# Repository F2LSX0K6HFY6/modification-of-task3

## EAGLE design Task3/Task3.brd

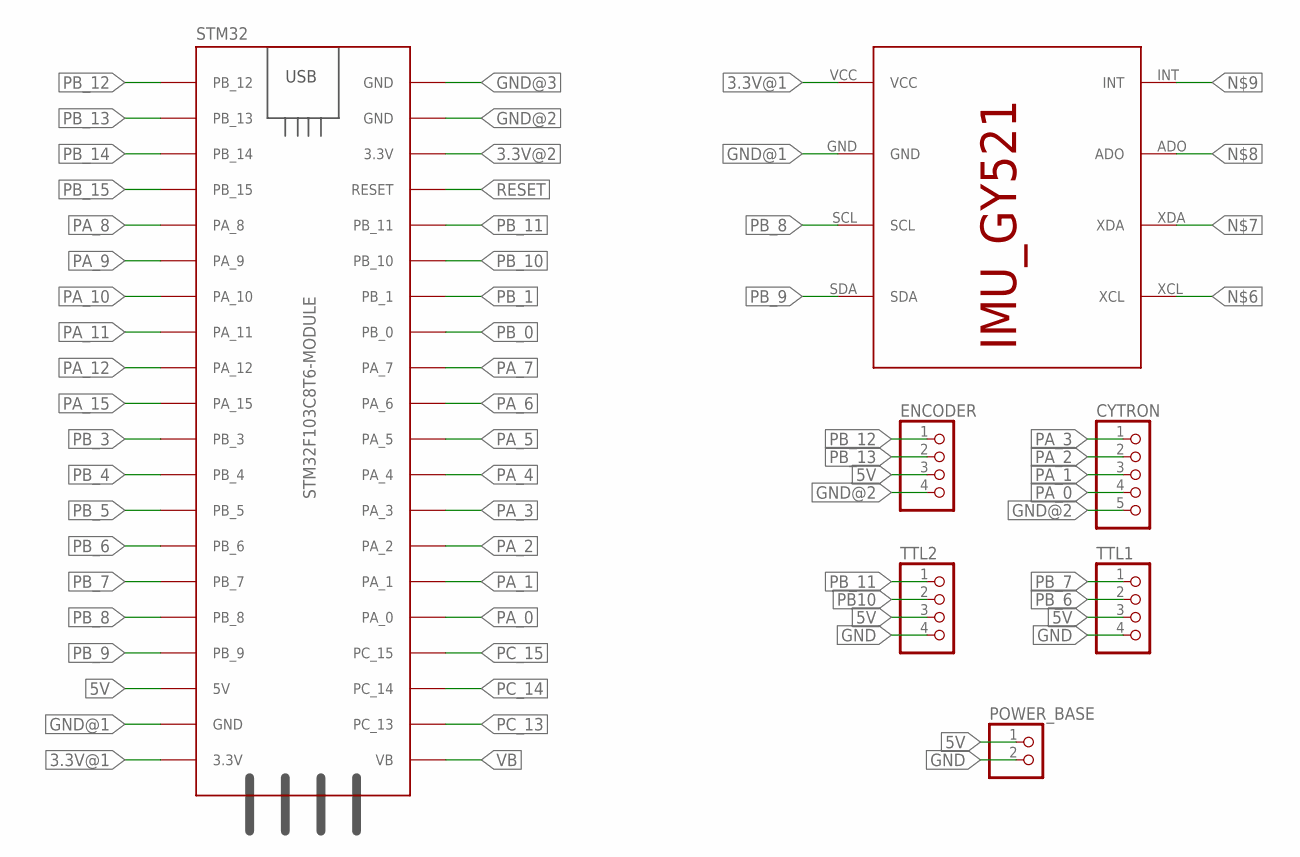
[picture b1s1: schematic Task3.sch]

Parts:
CYTRON: PINHD-5_DATA; 1X05_DATA
ENCODER: PINHD-4_DATA; 1X04_DATA
POWER_BASE: PINHD-2_DATA; 1X02_DATA
STM32: STM32F103C8T6-MODULE
TTL1, TTL2: PINHD-4_DATA; 1X04_DATA
U$1: IMU_ROBOCON_GY521; IMU_GY521

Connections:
3.3V@1: STM32.3.3V_1 (3.3V), U$1.VCC
3.3V@2: STM32.3.3V_2 (3.3V)
5V: ENCODER.3, POWER_BASE.1, STM32.5V, TTL1.3, TTL2.3
GND: POWER_BASE.2, TTL1.4, TTL2.4
GND@1: STM32.GND_1 (GND), U$1.GND
GND@2: CYTRON.5, ENCODER.4, STM32.GND_2 (GND)
GND@3: STM32.GND_3 (GND)
PA_0: CYTRON.4, STM32.PA_0
PA_1: CYTRON.3, STM32.PA_1
PA_2: CYTRON.2, STM32.PA_2
PA_3: CYTRON.1, STM32.PA_3
PA_4: STM32.PA_4
PA_5: STM32.PA_5
PA_6: STM32.PA_6
PA_7: STM32.PA_7
PA_8: STM32.PA_8
PA_9: STM32.PA_9
PA_10: STM32.PA_10
PA_11: STM32.PA_11
PA_12: STM32.PA_12
PA_15: STM32.PA_15
PB10: TTL2.2
PB_0: STM32.PB_0
PB_1: STM32.PB_1
PB_3: STM32.PB_3
PB_4: STM32.PB_4
PB_5: STM32.PB_5
PB_6: STM32.PB_6, TTL1.2
PB_7: STM32.PB_7, TTL1.1
PB_8: STM32.PB_8, U$1.SCL
PB_9: STM32.PB_9, U$1.SDA
PB_10: STM32.PB_10
PB_11: STM32.PB_11, TTL2.1
PB_12: ENCODER.1, STM32.PB_12
PB_13: ENCODER.2, STM32.PB_13
PB_14: STM32.PB_14
PB_15: STM32.PB_15
PC_13: STM32.PC_13
PC_14: STM32.PC_14
PC_15: STM32.PC_15
RESET: STM32.RESET
VB: STM32.VB

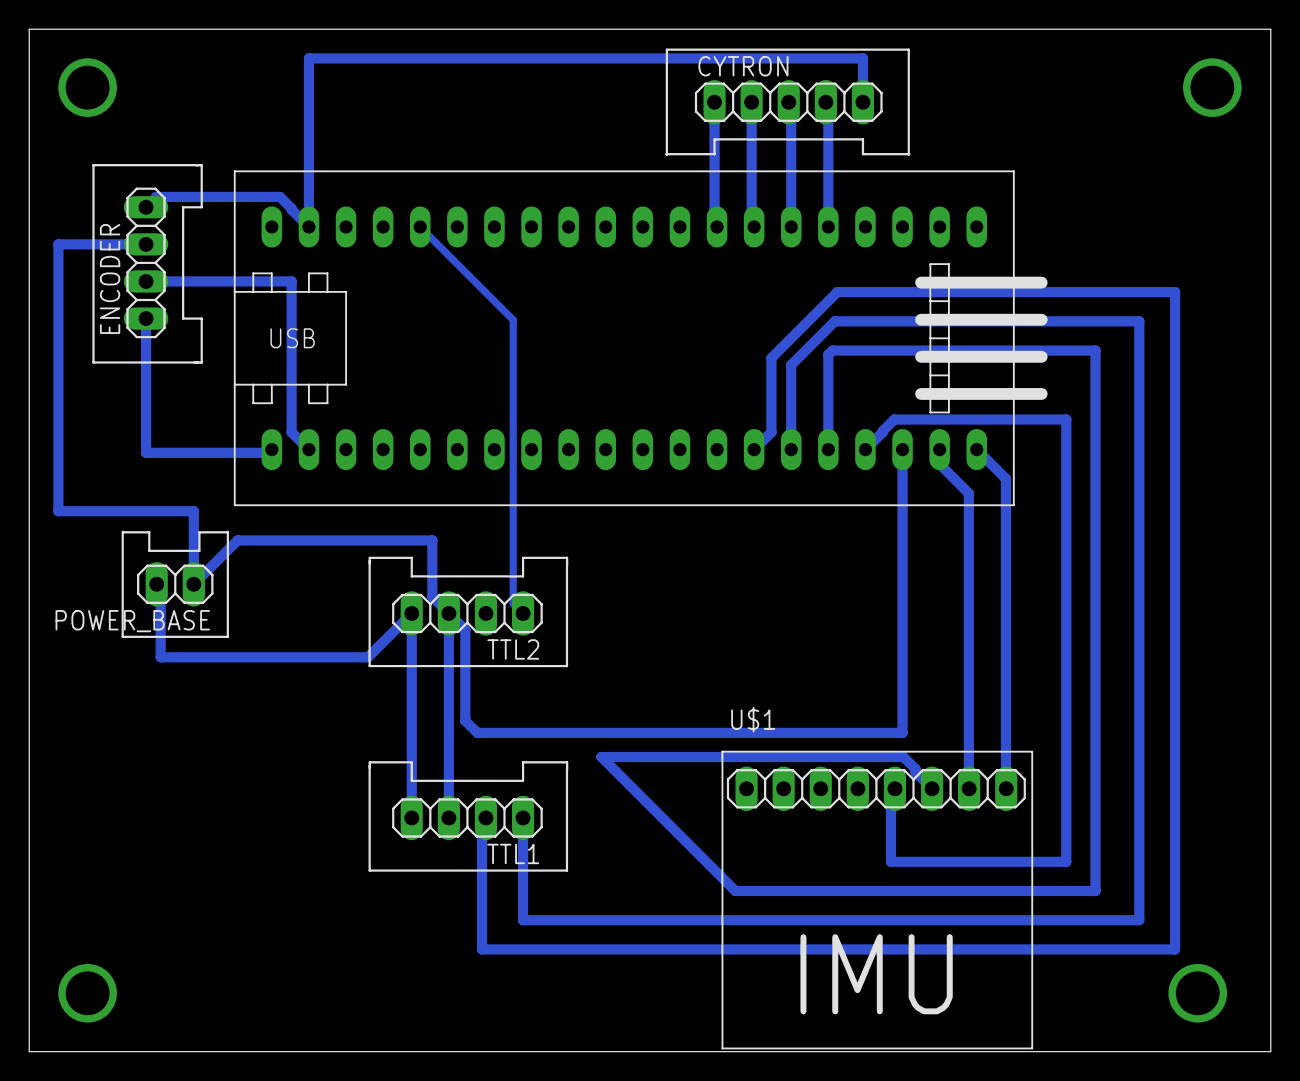
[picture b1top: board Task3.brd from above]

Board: 2 copper layers, 85.0 x 70.0 mm, 7 parts (0 on the bottom side), 16 nets.
